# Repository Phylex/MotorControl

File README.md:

MotorControl
============
This Repository has the Kicad source files for an H-Bridge that I want to use in my model RC Boats.
It is based around the DRV8701P H-Bridge driver Chip.

It's used in conjunction with Infineon IDP060N03L-G Mosfets with an Rd-on of 6 mOhm, so they should be good up to around 40-50 Amps.

Features
--------
It's main Features are: 
1. Current measurement via a Shunt resistor.

2. Reverse polarity protection. 

3. A settable maximum current (courtesy of current chopping of the DRV8701)

4. The input current is smoothed via an inductor/capacitor combination of 2.2uH/440uF respectively.

5. A maxixum operating PWM frequency of 50 kHz.

Notes
-----
1. According to my calculations and the voltage that is likely to power the Boats (2S Li-Ion battery packs) the maxixum PWM frequency that the charge pump
of the DRV8701P supports is 86kHz so far outside the problematic resonance frequency of 5.1 kHz of the Inductor/Capacitor current smoothing

2. The total gate charge of one MOSFET is < 14.4 nC which is roughly the number that the reference design in the Data sheet mentions.
In this case The current source for the high-side FETs is set to 100mA via a resistor on the board. This gives the FETs a worst case rise time of 144
ns.

3. The Resonance of the Inductor-Capacitor circuit is at roughly 5.1 kHz, so A PWM frequency a fair bit higher is recommended.)

4. The data sheet mentions a maxixum current chopping frequency of 38 kHz so well inside the maximum supported frequency.

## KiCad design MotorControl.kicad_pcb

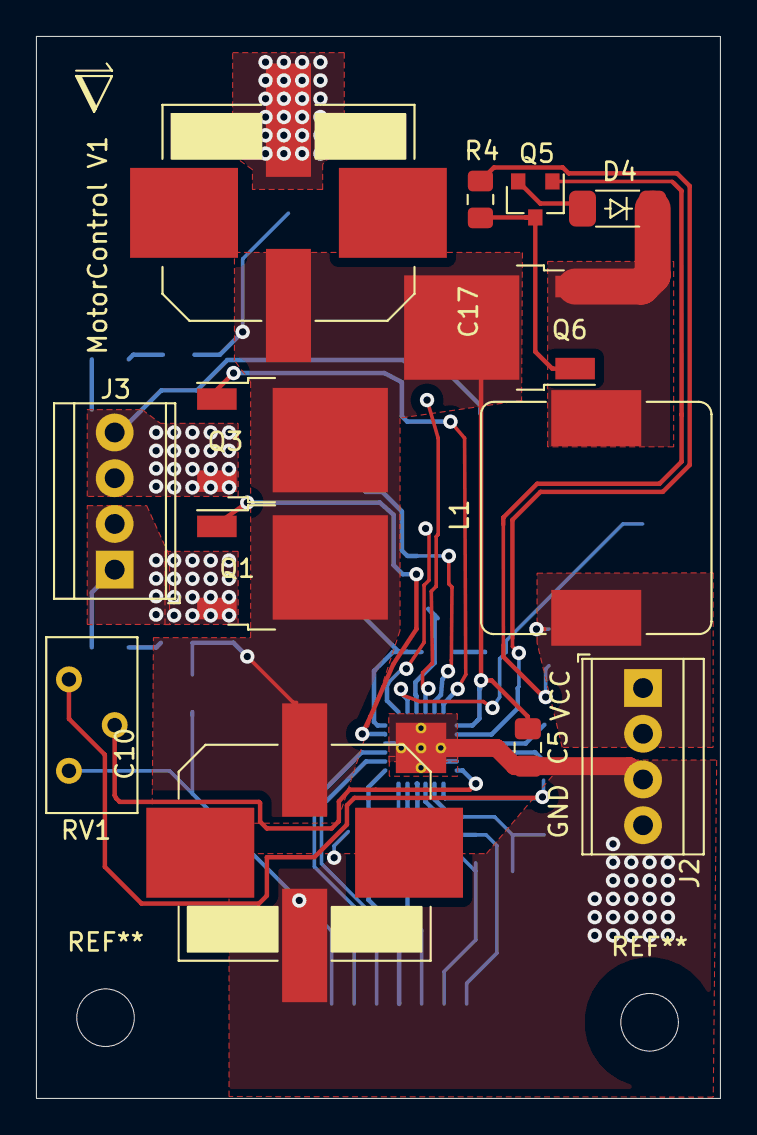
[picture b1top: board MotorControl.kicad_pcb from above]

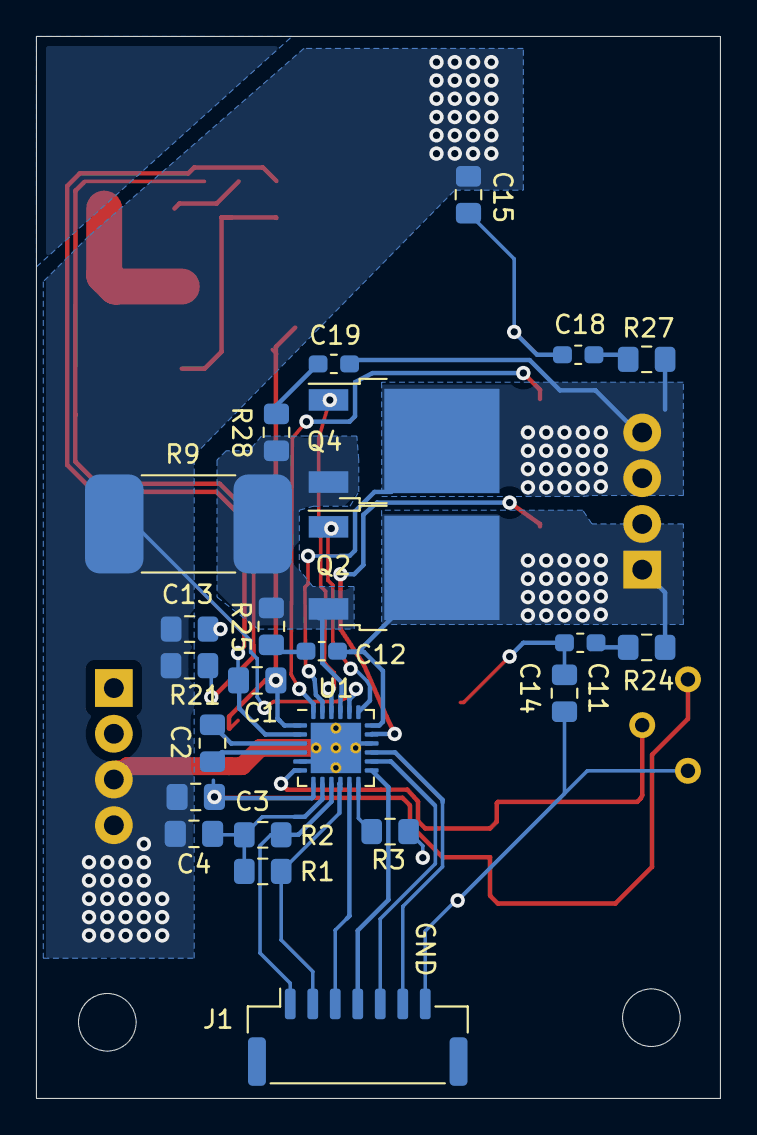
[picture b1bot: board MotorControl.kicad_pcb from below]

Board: 2 copper layers, 38.0 x 59.0 mm, 37 parts (24 on the bottom side), 31 nets.

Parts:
C1, C3, C4: 1uF; C_0805_2012Metric_Pad1.18x1.45mm_HandSolder
C2: 100nF; C_0805_2012Metric_Pad1.15x1.40mm_HandSolder
C5: 100nF; C_0805_2012Metric_Pad1.18x1.45mm_HandSolder
C10, C17: 220uf; Vishay_ELKO_1213
C11, C12, C18, C19: 4.7n; C_0603_1608Metric_Pad1.05x0.95mm_HandSolder
C13: 100n; C_0805_2012Metric_Pad1.15x1.40mm_HandSolder
C14, C15: 2.2uF; C_0805_2012Metric_Pad1.15x1.40mm_HandSolder
D4: BZT55C12; MELF_SOD-80
J1: Conn_01x07_Female; JST_GH_SM07B-GHS-TB_1x07-1MP_P1.25mm_Horizontal
J2, J3: Screw_Terminal_01x04; TerminalBlock_TE_282834-4_1x04_P2.54mm_Horizontal
L1: 2.2uH; L_Bourns_SRP1245A
Q1, Q2, Q3, Q4, Q6: IPD060N03L G; TO-252-2
Q5: BC846B,215; SOT-23
R1, R2, R4: 10K; R_0805_2012Metric_Pad1.15x1.40mm_HandSolder
R3: 1G; R_0805_2012Metric_Pad1.15x1.40mm_HandSolder
R9: 3m; TE_LRS1050
R21: 47k; R_0805_2012Metric_Pad1.15x1.40mm_HandSolder
R24, R25, R27, R28: 2; R_0805_2012Metric_Pad1.15x1.40mm_HandSolder
RV1: 200K; Potentiometer_Bourns_3386X_Horizontal
U1: DRV8701P; QFN-24-1EP_4x4mm_P0.5mm_EP2.8x2.8mm_ThermalVias

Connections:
/AVDD: C3.1, RV1.1, U1.7
/DVDD: C4.1, R1.1, R2.1, U1.8
/GH1: Q1.1, U1.17
/GH2: Q3.1, U1.24
/GL1: Q2.1, U1.19
/GL2: Q4.1, U1.22
/IN1: J1.6, U1.15
/IN2: J1.5, U1.14
/MOTL: C12.1, J3.1, J3.2, Q1.3, Q2.2, R24.2, U1.18
/MOTR: C19.1, J3.3, J3.4, Q3.3, Q4.2, R27.2, U1.23
/SL: Q2.3, Q4.3, R9.2, R25.2, R28.2, U1.21
/SNSOUT: J1.2, R1.2, U1.10
/SO: J1.3, U1.11
/nFAULT: J1.1, R2.2, U1.9
/nSLEEP: J1.4, U1.13
GND: C3.2, C4.2, C5.2, C10.2, C13.2, C14.2, C15.1, C17.2, J1.7, J2.3, J2.4, R3.2, R9.1, R21.2, RV1.3, U1.5, U1.16, U1.20, U1.25
unnamed: C1.1, R4.2, U1.2
unnamed: C1.2, C5.1, C10.1, C11.1, C14.1, C15.2, C17.1, C18.1, Q1.2, Q3.2, Q6.2, U1.1
unnamed: C2.1, U1.3
unnamed: C2.2, U1.4
unnamed: C11.2, R24.1
unnamed: C12.2, R25.1
unnamed: C18.2, R27.1
unnamed: C19.2, R28.1
unnamed: D4.1, L1.2, Q6.3
unnamed: D4.2, Q5.2
unnamed: Q5.1, R21.1
unnamed: Q5.3, Q6.1, R4.1
unnamed: R3.1, U1.12
unnamed: RV1.2, U1.6
VPP: C13.1, J2.1, J2.2, L1.1

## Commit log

2021-06-02 added the designs files and a proper Readme
2021-06-02 added the project file
